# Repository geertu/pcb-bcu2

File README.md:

# BCU/2 - Board Control Unit Duo (KiCad PCB)

This is a small board to control operation of two development boards, e.g. on
your desk, or in a board farm.

## Features

  - Controlled by a Teensy 3.2 (https://www.pjrc.com/store/teensy32.html),
  - Two power control and measurement channels (3.3-14V, max. 3.2A),
  - Two UART channels
      - Optional buffer circuitry supports 1.8 to 5V, or fixed 3.3V,
      - Add external MAX3232 board for RS232-compatible voltage levels.
  - Six opto-isolators for e.g. reset, wake-up, and keypress simulation,
  - Two RGB status LEDs,
  - 4-pin I2C expansion connector,
  - 4-pin GPIO expansion connector.

## Software

Software to run on the Teensy is available from
https://github.com/geertu/teensy3-bcu2 in source form.

## License

CC-BY-SA-4.0 (https://creativecommons.org/licenses/by-sa/4.0/)

## PCB and Parts

PCB and parts can be ordered at
https://aisler.net/geert/board-control-unit/bcu-2 (Disclaimer: I'm not
affiliated to AISLER)

## Bill Of Materials

  - C1-C4[A], C5-C7, C9: Capacitor, 100nF, SMD 0603/1608
  - C8, C10-C12: Capacitor, 10µF, SMD 0805/2012, 25V
  - D1, D2: LED RGB Diffused, Common Anode at pin 1, SMD 4PLCC
  - D3, D6-D10: LED Yellow clear, SMD 0603/1608
  - D4, D5: LED Green clear, SMD 0603/1608
  - J1, J3: Screw type, terminal block, RM 3.5mm
  - J2: Male 1x12 header 2.54mm
  - J4, J5: Male 1x5 header, RM 2.54mm
  - J6, J7: Male 1x4 header, RM 2mm, e.g. JST B4B-PH-K
  - J8-J9[B]: Male 1x14 header, RM 2.54mm
  - J10-J11[B]: Female 1x14 header, RM 2.54mm
  - Q1, Q3, Q4, Q6: MOSFET N-channel 60V 115mA, SOT23-3
  - Q2, Q5: MOSFET P-channel 20V 10A, SOT223
  - R1, R4: Resistor, 680Ω, SMD 0603/1608
  - R2, R3, R5, R6: Resistor, 100Ω, SMD 0603/1608
  - R7, R13, R18, R19, R21, R23, R25, R27: Resistor, 1kΩ, SMD 0603/1608
  - R8, R20, R22, R24, R26, R28: Resistor, 270Ω, SMD 0603/1608
  - R9, R14: Resistor, 10kΩ, SMD 0603/1608
  - R10, R11, R15, R16, R37[A], R38[A]: Resistor, 47kΩ, SMD 0603/1608
  - R12, R17: Resistor, 100kΩ, SMD 0603/1608
  - R29-R32[C]: Resistor, 0Ω, SMD 0603/1608
  - R33, R34: Resistor, 100mΩ, SMD 2512/6432, 1%, 2W
  - R35, R36: Resistor, 4.7kΩ, SMD 0603/1608
  - U1: Teensy 3.2
  - U2-U7: Opto-isolator, Mini-Flat-4, e.g. Broadcom HCPL-181-00CE
  - U8-U11[A]: 2-input AND gate 74LV1T08[D], SOT23-5
  - U12, U13: INA219xID power monitor, 8-SOIC

## Connector pinouts

  - J1 / J3: Power channels A & B

    Pin | Function
    --- | --------
     1  | GND
     2  | Power OUT
     3  | GND
     4  | Power IN (3.3-14V, max. 3.2A)

  - J2: Opto-isolator channels 0-5

    Pin               | Function
    ----------------- | --------
     1-11 (odd pins)  | Emitter ("negative output")
     2-12 (even pins) | Collector ("positive output")

  - J4 / J5: UART channels A & B

    Pin | Function
    --- | --------
     1  | GND
     2  | RXD
     3  | TXD
     4  | VBUS (1.8V to 5V), may be jumpered to +3V3
     5  | +3.3V[E]

  - J6: I2C expansion[F]

    Pin | Function
    --- | --------
     1  | GND
     2  | +3.3V[E]
     3  | SDA
     4  | SCL

  - J7: GPIO expansion[F]

    Pin | Function
    --- | --------
     1  | GND
     2  | +3.3V[E]
     3  | GPIO0
     4  | GPIO1

## Footnotes

  * [A] Optional buffer circuitry, mutually exclusive with [C]
  * [B] For Teensy plugin, not on schematic
  * [C] Optional buffer bypass, mutually exclusive with [A]
  * [D] Replace by 74LV1T00 for inverted TXD/RXD logic
  * [E] Maximum current output on the +3.3V pin of the Teensy 3.2 is 250 mA.
	Up to 100-125 mA can be used by expansion peripherals.
  * [F] Pin order of the I2C and GPIO expansion connectors is similar (but
	reversed!) to the Seeed Studio Grove and SparkFun Qwiic Connect
	systems, although the connector used is different (you can probably
	mount a real Grove connector instead).

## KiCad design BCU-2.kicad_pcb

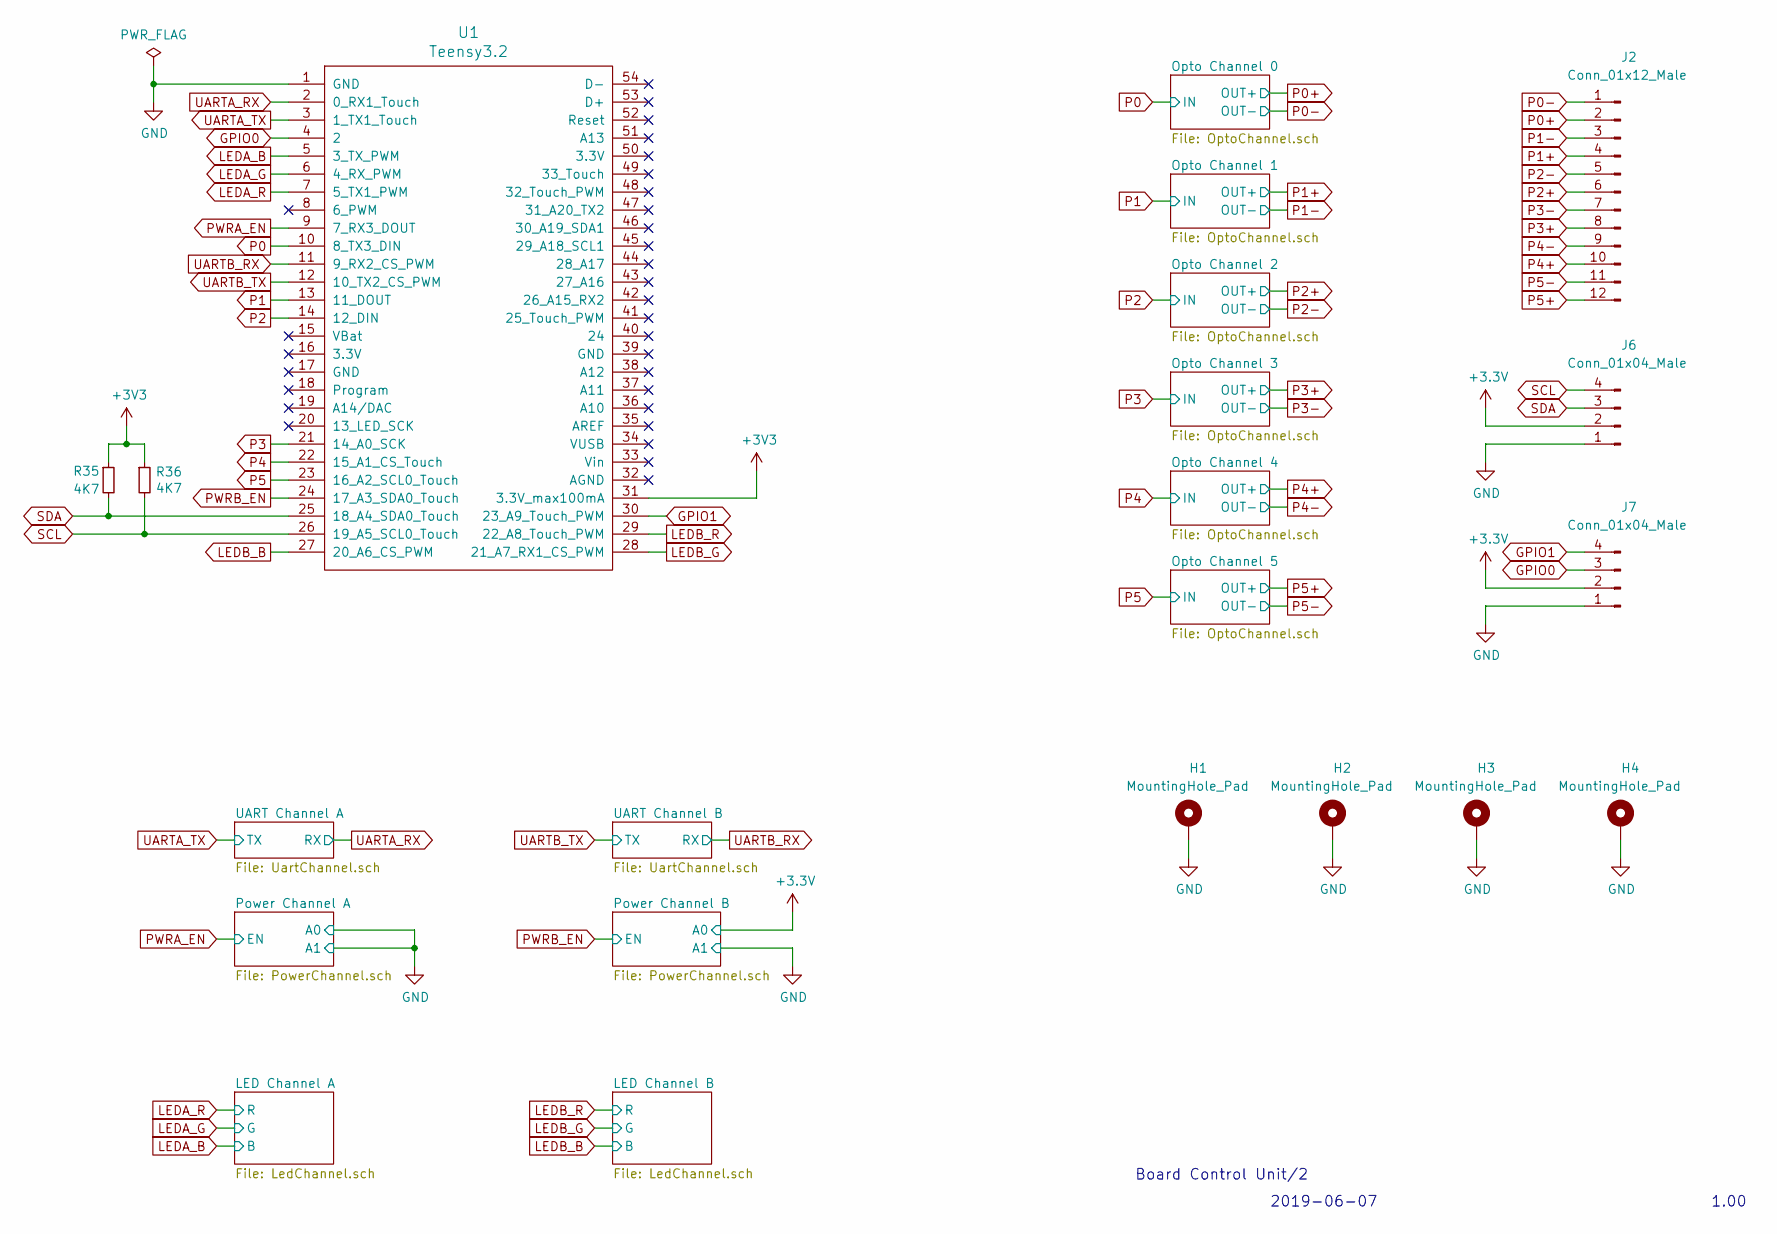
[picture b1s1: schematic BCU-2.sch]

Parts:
H1, H2, H3, H4: MountingHole_Pad; MountingHole_3.2mm_M3_DIN965_Pad
J2: Conn_01x12_Male; PinHeader_1x12_P2.54mm_Vertical
J6, J7: Conn_01x04_Male; JST_PH_B4B-PH-K_1x04_P2.00mm_Vertical
R35, R36: 4K7; R_0603_1608Metric_Pad1.05x0.95mm_HandSolder
U1: Teensy3.2; Teensy32-DIP28

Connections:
+3V3: J6.2, J7.2, R35.1, R36.1, U1.31 (3.3V_max100mA); also elsewhere on the board
GND: H1.1, H2.1, H3.1, H4.1, J6.1, J7.1, U1.1 (GND); also elsewhere on the board
GPIO0: J7.3, U1.4 (2)
GPIO1: J7.4, U1.30 (23_A9_Touch_PWM)
LEDA_B: U1.5 (3_TX_PWM); also elsewhere on the board
LEDA_G: U1.6 (4_RX_PWM); also elsewhere on the board
LEDA_R: U1.7 (5_TX1_PWM); also elsewhere on the board
LEDB_B: U1.27 (20_A6_CS_PWM); also elsewhere on the board
LEDB_G: U1.28 (21_A7_RX1_CS_PWM); also elsewhere on the board
LEDB_R: U1.29 (22_A8_Touch_PWM); also elsewhere on the board
P0: U1.10 (8_TX3_DIN); also elsewhere on the board
P0+: J2.2; also elsewhere on the board
P0-: J2.1; also elsewhere on the board
P1: U1.13 (11_DOUT); also elsewhere on the board
P1+: J2.4; also elsewhere on the board
P1-: J2.3; also elsewhere on the board
P2: U1.14 (12_DIN); also elsewhere on the board
P2+: J2.6; also elsewhere on the board
P2-: J2.5; also elsewhere on the board
P3: U1.21 (14_A0_SCK); also elsewhere on the board
P3+: J2.8; also elsewhere on the board
P3-: J2.7; also elsewhere on the board
P4: U1.22 (15_A1_CS_Touch); also elsewhere on the board
P4+: J2.10; also elsewhere on the board
P4-: J2.9; also elsewhere on the board
P5: U1.23 (16_A2_SCL0_Touch); also elsewhere on the board
P5+: J2.12; also elsewhere on the board
P5-: J2.11; also elsewhere on the board
PWRA_EN: U1.9 (7_RX3_DOUT); also elsewhere on the board
PWRB_EN: U1.24 (17_A3_SDA0_Touch); also elsewhere on the board
SCL: J6.4, R36.2, U1.26 (19_A5_SCL0_Touch); also elsewhere on the board
SDA: J6.3, R35.2, U1.25 (18_A4_SDA0_Touch); also elsewhere on the board
UARTA_RX: U1.2 (0_RX1_Touch); also elsewhere on the board
UARTA_TX: U1.3 (1_TX1_Touch); also elsewhere on the board
UARTB_RX: U1.11 (9_RX2_CS_PWM); also elsewhere on the board
UARTB_TX: U1.12 (10_TX2_CS_PWM); also elsewhere on the board

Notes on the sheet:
Board Control Unit/2
2019-06-07
1.00

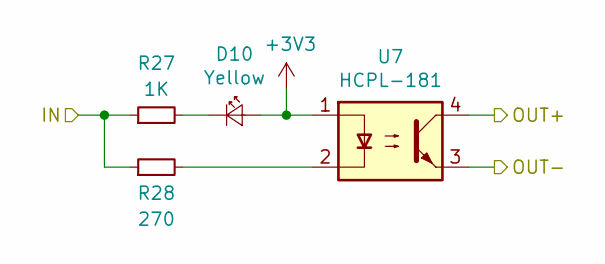
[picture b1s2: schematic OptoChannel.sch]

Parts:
D3: Yellow; LED_0603_1608Metric_Castellated
R7: 1K; R_0603_1608Metric_Pad1.05x0.95mm_HandSolder
R8: 270; R_0603_1608Metric_Pad1.05x0.95mm_HandSolder
U2: HCPL-181; SMDIP-4_W7.62mm

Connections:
+3V3: D3.2 (A), U2.1; also elsewhere on the board
unnamed: D3.1 (K), R7.2
unnamed: R8.2, U2.2
P0: R7.1, R8.1; also elsewhere on the board
P0+: U2.4; also elsewhere on the board
P0-: U2.3; also elsewhere on the board

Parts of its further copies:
D6, D7, D8, D9, D10: Yellow; LED_0603_1608Metric_Castellated
R19, R21, R23, R25, R27: 1K; R_0603_1608Metric_Pad1.05x0.95mm_HandSolder
R20, R22, R24, R26, R28: 270; R_0603_1608Metric_Pad1.05x0.95mm_HandSolder
U3, U4, U5, U6, U7: HCPL-181; SMDIP-4_W7.62mm

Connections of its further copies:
+3V3: D6.2 (A), D7.2 (A), D8.2 (A), D9.2 (A), D10.2 (A), U3.1, U4.1, U5.1, U6.1, U7.1; also elsewhere on the board
unnamed: D6.1 (K), R19.2
unnamed: D7.1 (K), R21.2
unnamed: D8.1 (K), R23.2
unnamed: D9.1 (K), R25.2
unnamed: D10.1 (K), R27.2
unnamed: R20.2, U3.2
unnamed: R22.2, U4.2
unnamed: R24.2, U5.2
unnamed: R26.2, U6.2
unnamed: R28.2, U7.2
P1: R19.1, R20.1; also elsewhere on the board
P1+: U3.4; also elsewhere on the board
P1-: U3.3; also elsewhere on the board
P2: R21.1, R22.1; also elsewhere on the board
P2+: U4.4; also elsewhere on the board
P2-: U4.3; also elsewhere on the board
P3: R23.1, R24.1; also elsewhere on the board
P3+: U5.4; also elsewhere on the board
P3-: U5.3; also elsewhere on the board
P4: R25.1, R26.1; also elsewhere on the board
P4+: U6.4; also elsewhere on the board
P4-: U6.3; also elsewhere on the board
P5: R27.1, R28.1; also elsewhere on the board
P5+: U7.4; also elsewhere on the board
P5-: U7.3; also elsewhere on the board

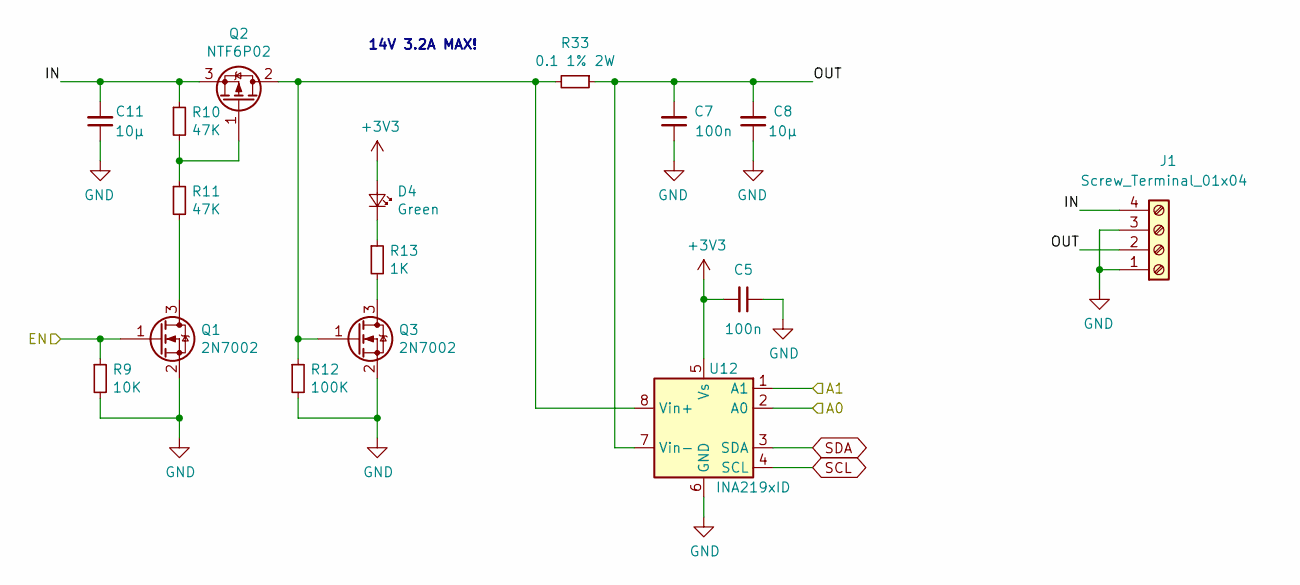
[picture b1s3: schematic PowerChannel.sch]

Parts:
C6, C9: 100n; C_0603_1608Metric_Pad1.05x0.95mm_HandSolder
C10, C12: 10µ; C_0805_2012Metric_Pad1.15x1.40mm_HandSolder
D4: Green; LED_0603_1608Metric_Castellated
J1: Screw_Terminal_01x04; TerminalBlock_MetzConnect_Type059_RT06304HBWC_1x04_P3.50mm_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
Q1, Q3: 2N7002; SOT-23_Handsoldering
Q2: NTF6P02; SOT-223-3_TabPin2
R9: 10K; R_0603_1608Metric_Pad1.05x0.95mm_HandSolder
R10, R11: 47K; R_0603_1608Metric_Pad1.05x0.95mm_HandSolder
R12: 100K; R_0603_1608Metric_Pad1.05x0.95mm_HandSolder
R13: 1K; R_0603_1608Metric_Pad1.05x0.95mm_HandSolder
R34: 0.1 1% 2W; R_2512_6332Metric_Pad1.52x3.35mm_HandSolder
U12: INA219xID; SOIC-8_3.9x4.9mm_P1.27mm

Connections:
+3V3: C6.2, D4.2 (A), U12.5 (Vs); also elsewhere on the board
GND: C6.1, C9.1, C10.1, C12.1, J1.1, J1.3, Q1.2 (S), Q3.2 (S), R9.2, R12.2, U12.1 (A1), U12.2 (A0), U12.6 (GND); also elsewhere on the board
unnamed: D4.1 (K), R13.1
unnamed: Q1.3 (D), R11.2
unnamed: Q2.1 (G), R10.2, R11.1
unnamed: Q3.3 (D), R13.2
PWRA_EN: Q1.1 (G), R9.1; also elsewhere on the board
SCL: U12.4 (SCL); also elsewhere on the board
SDA: U12.3 (SDA); also elsewhere on the board

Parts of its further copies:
C5, C7: 100n; C_0603_1608Metric_Pad1.05x0.95mm_HandSolder
C8, C11: 10µ; C_0805_2012Metric_Pad1.15x1.40mm_HandSolder
D5: Green; LED_0603_1608Metric_Castellated
J3: Screw_Terminal_01x04; TerminalBlock_MetzConnect_Type059_RT06304HBWC_1x04_P3.50mm_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
Q4, Q6: 2N7002; SOT-23_Handsoldering
Q5: NTF6P02; SOT-223-3_TabPin2
R14: 10K; R_0603_1608Metric_Pad1.05x0.95mm_HandSolder
R15, R16: 47K; R_0603_1608Metric_Pad1.05x0.95mm_HandSolder
R17: 100K; R_0603_1608Metric_Pad1.05x0.95mm_HandSolder
R18: 1K; R_0603_1608Metric_Pad1.05x0.95mm_HandSolder
R33: 0.1 1% 2W; R_2512_6332Metric_Pad1.52x3.35mm_HandSolder
U13: INA219xID; SOIC-8_3.9x4.9mm_P1.27mm

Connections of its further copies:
+3V3: C5.2, D5.2 (A), U13.2 (A0), U13.5 (Vs); also elsewhere on the board
GND: C5.1, C7.1, C8.1, C11.1, J3.1, J3.3, Q4.2 (S), Q6.2 (S), R14.2, R17.2, U13.1 (A1), U13.6 (GND); also elsewhere on the board
unnamed: D5.1 (K), R18.1
unnamed: Q4.3 (D), R16.2
unnamed: Q5.1 (G), R15.2, R16.1
unnamed: Q6.3 (D), R18.2
PWRB_EN: Q4.1 (G), R14.1; also elsewhere on the board
SCL: U13.4 (SCL); also elsewhere on the board
SDA: U13.3 (SDA); also elsewhere on the board

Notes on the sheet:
14V 3.2A MAX!

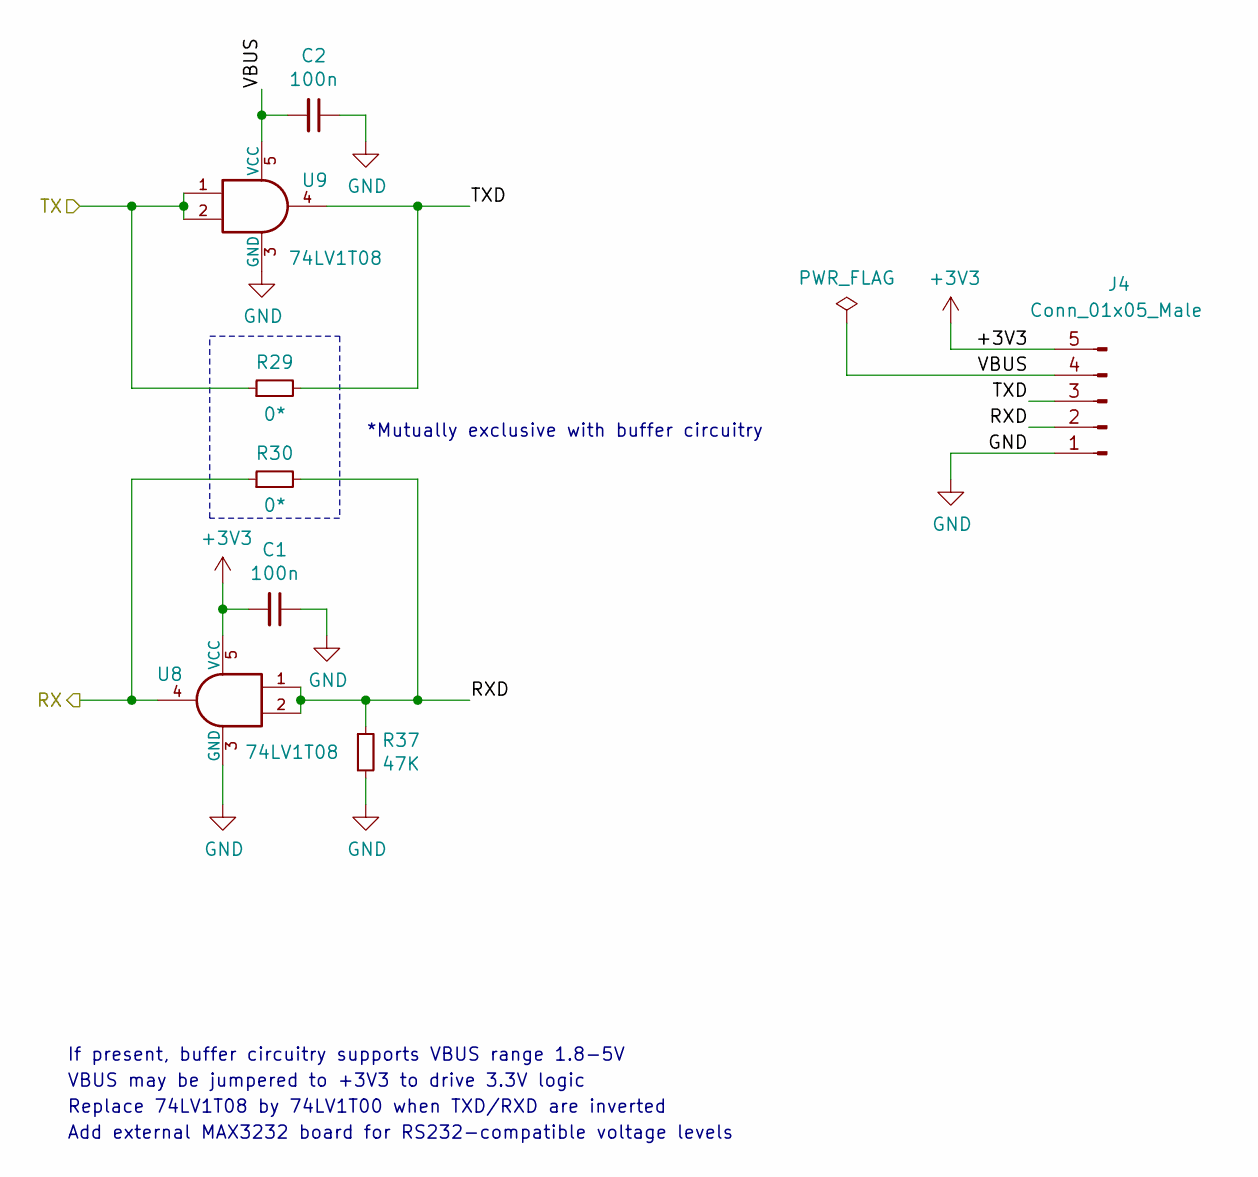
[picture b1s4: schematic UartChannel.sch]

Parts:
C1, C2: 100n; C_0603_1608Metric_Pad1.05x0.95mm_HandSolder
J4: Conn_01x05_Male; PinHeader_1x05_P2.54mm_Vertical
R29, R30: 0*; R_0603_1608Metric_Pad1.05x0.95mm_HandSolder
R37: 47K; R_0603_1608Metric_Pad1.05x0.95mm_HandSolder
U8, U9: 74LV1T08; SOT-23-5_HandSoldering

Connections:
+3V3: C1.2, J4.5, U8.5 (VCC); also elsewhere on the board
/UART Channel A/RXD: J4.2, R30.2, R37.1, U8.1, U8.2
/UART Channel A/TXD: J4.3, R29.2, U9.4
/UART Channel A/VBUS: C2.2, J4.4, U9.5 (VCC)
GND: C1.1, C2.1, J4.1, R37.2, U8.3 (GND), U9.3 (GND); also elsewhere on the board
UARTA_RX: R30.1, U8.4; also elsewhere on the board
UARTA_TX: R29.1, U9.1, U9.2; also elsewhere on the board

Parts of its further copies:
C3, C4: 100n; C_0603_1608Metric_Pad1.05x0.95mm_HandSolder
J5: Conn_01x05_Male; PinHeader_1x05_P2.54mm_Vertical
R31, R32: 0*; R_0603_1608Metric_Pad1.05x0.95mm_HandSolder
R38: 47K; R_0603_1608Metric_Pad1.05x0.95mm_HandSolder
U10, U11: 74LV1T08; SOT-23-5_HandSoldering

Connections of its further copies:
+3V3: C3.2, J5.5, U10.5 (VCC); also elsewhere on the board
/UART Channel B/RXD: J5.2, R32.2, R38.1, U10.1, U10.2
/UART Channel B/TXD: J5.3, R31.2, U11.4
/UART Channel B/VBUS: C4.2, J5.4, U11.5 (VCC)
GND: C3.1, C4.1, J5.1, R38.2, U10.3 (GND), U11.3 (GND); also elsewhere on the board
UARTB_RX: R32.1, U10.4; also elsewhere on the board
UARTB_TX: R31.1, U11.1, U11.2; also elsewhere on the board

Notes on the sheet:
*Mutually exclusive with buffer circuitry
If present, buffer circuitry supports VBUS range 1.8-5V
Replace 74LV1T08 by 74LV1T00 when TXD/RXD are inverted
VBUS may be jumpered to +3V3 to drive 3.3V logic
Add external MAX3232 board for RS232-compatible voltage levels

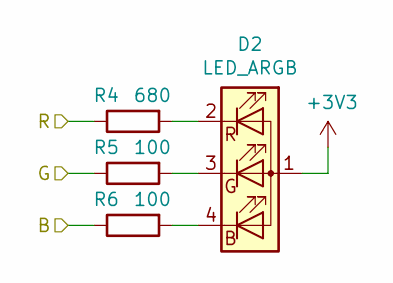
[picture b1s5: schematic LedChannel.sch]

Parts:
D1: LED_ARGB; LED_Cree-PLCC4_3.2x2.8mm_CCW
R1: 680; R_0603_1608Metric_Pad1.05x0.95mm_HandSolder
R2, R3: 100; R_0603_1608Metric_Pad1.05x0.95mm_HandSolder

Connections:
+3V3: D1.1 (A); also elsewhere on the board
LEDA_B: R3.1; also elsewhere on the board
LEDA_G: R2.1; also elsewhere on the board
LEDA_R: R1.1; also elsewhere on the board
unnamed: D1.2 (RK), R1.2
unnamed: D1.3 (GK), R2.2
unnamed: D1.4 (BK), R3.2

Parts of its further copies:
D2: LED_ARGB; LED_Cree-PLCC4_3.2x2.8mm_CCW
R4: 680; R_0603_1608Metric_Pad1.05x0.95mm_HandSolder
R5, R6: 100; R_0603_1608Metric_Pad1.05x0.95mm_HandSolder

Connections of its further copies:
+3V3: D2.1 (A); also elsewhere on the board
LEDB_B: R6.1; also elsewhere on the board
LEDB_G: R5.1; also elsewhere on the board
LEDB_R: R4.1; also elsewhere on the board
unnamed: D2.2 (RK), R4.2
unnamed: D2.3 (GK), R5.2
unnamed: D2.4 (BK), R6.2

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
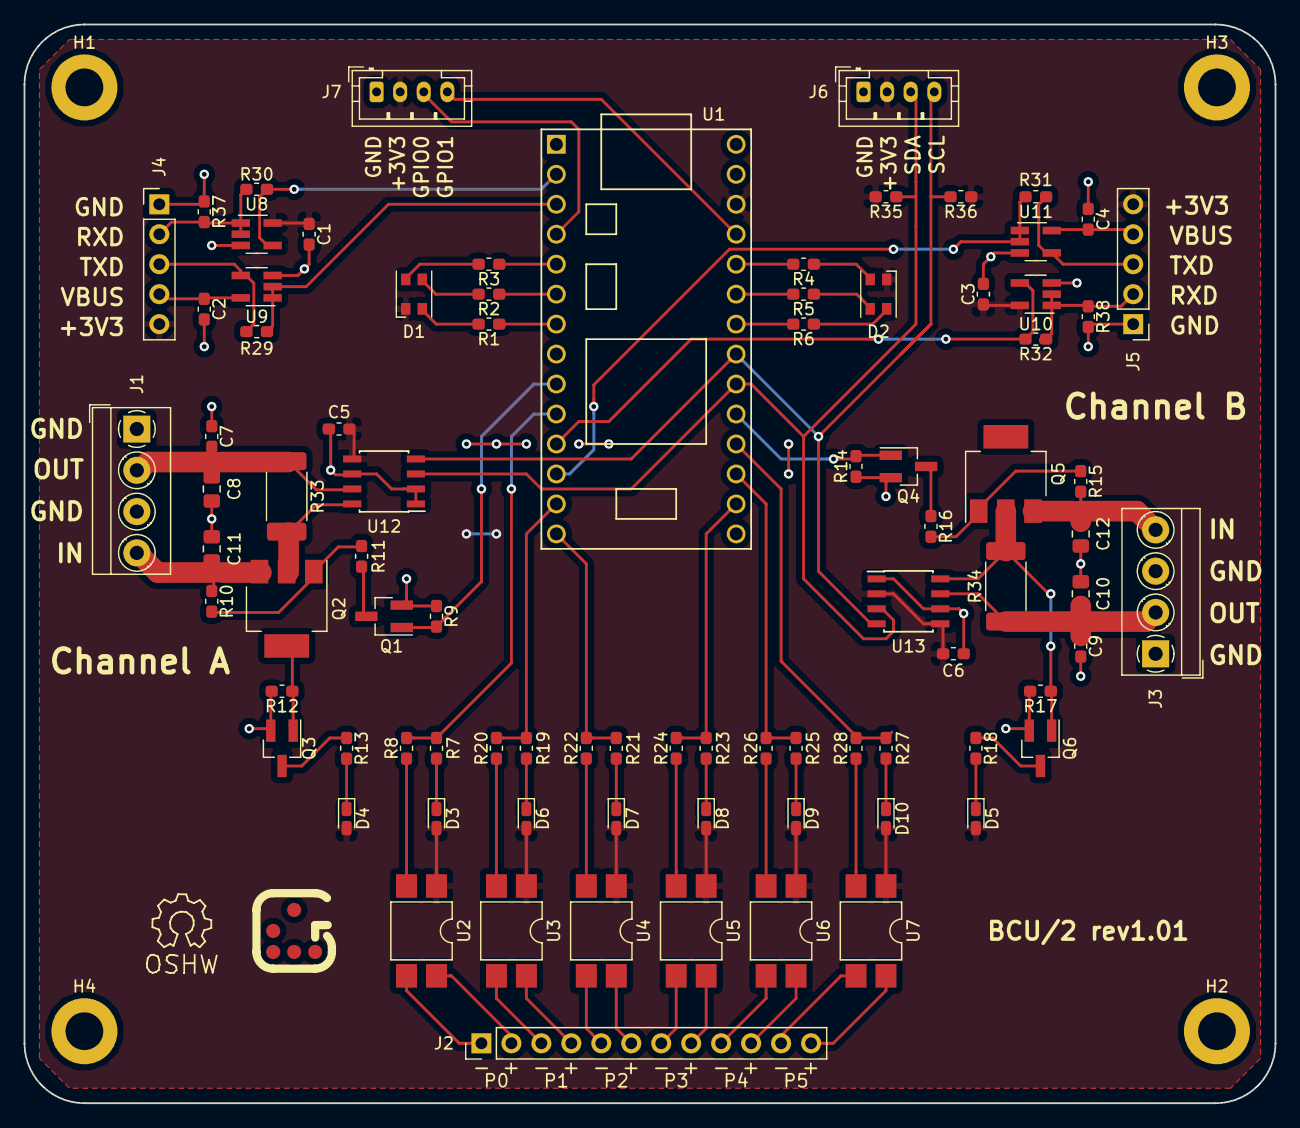
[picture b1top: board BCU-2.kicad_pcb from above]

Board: 2 copper layers, 106.0 x 91.4 mm, 92 parts (0 on the bottom side), 74 nets.

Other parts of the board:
Glider: Glider logo; Glider_bvba_G_Medium
OSHW: Symbol_OSHW-Logo_SilkScreen

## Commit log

2019-06-12 Import 74LV1T08 component (single AND gate)
    Including power pins.
2019-06-12 Import INA219 component (SOIC-8 version)
    Warning: the SOT-23 version has a mirrored pinout!
2019-06-12 Initial project commit
2019-06-12 Import schematic and PCB
2020-02-12 Enhance README.md
2020-02-12 Add link to project at AISLER
2020-02-13 Use tables for connector pinouts
2020-02-14 Add PCB image
2020-02-14 Use Markdown sections
2022-11-25 Improve silkscreen for rev1.01
